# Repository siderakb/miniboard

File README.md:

# Miniboard

A super mini keyboard.

## Disclaimer

These files are provided without warranty of any kind.  
Including but not limited to manufacturing, assembly, procurement and use at your own risk.  
It is recommended to check yourself before use.  

For the full statement, please see [LICENSE](./LICENSE).

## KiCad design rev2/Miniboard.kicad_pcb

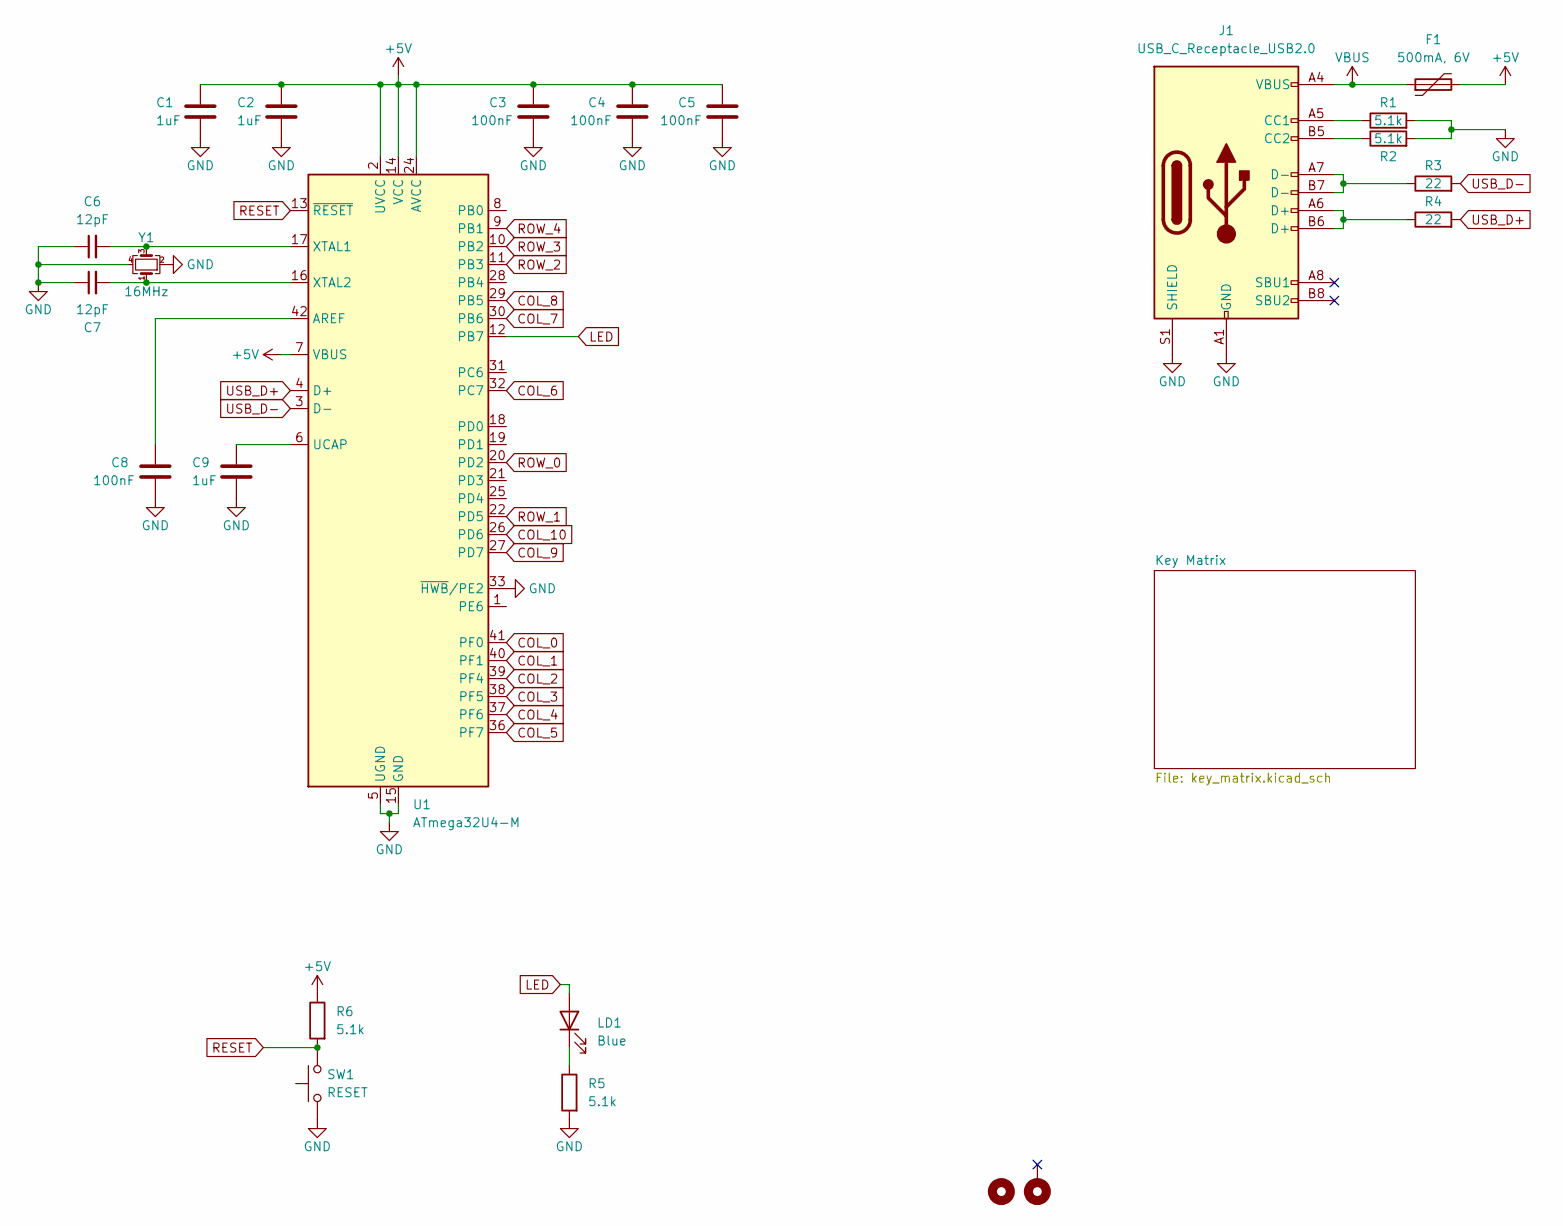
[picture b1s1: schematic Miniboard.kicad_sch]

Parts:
C1, C2, C9: 1uF; C_0402_1005Metric; MFR. Part # CL05A105KA5NQNC; LCSC C52923
C3, C4, C5, C8: 100nF; C_0402_1005Metric; MFR. Part # CL05B104KO5NNNC; LCSC C1525
C6, C7: 12pF; C_0402_1005Metric; MFR. Part # 0402CG120J500NT; LCSC C1547
F1: 500mA, 6V; Fuse_0805_2012Metric; MFR. Part # SMD0805B050TF; LCSC C269104
H2: MountingHole
H3: MountingHole_Pad; MountingHole_2.2mm_M2_DIN965_Pad
J1: USB_C_Receptacle_USB2.0; USB-C_16p_918-418K2023S40023; MFR. Part # 918-418K2023S40023; LCSC C709031
LD1: Blue; LED_0603_1608Metric; MFR. Part # 19-217/GHC-YR1S2/3T; LCSC C72043
R1, R2, R5, R6: 5.1k; R_0402_1005Metric; MFR. Part # 0402WGF5101TCE; LCSC C25905
R3, R4: 22; R_0402_1005Metric; MFR. Part # CRCW040222R0FKED; LCSC C482106
SW1: RESET; SW_SPST_B3U-1000P; MFR. Part # B3U-1000P; LCSC C231329
U1: ATmega32U4-M; QFN-44-1EP_7x7mm_P0.5mm_EP5.2x5.2mm; MFR. Part # ATMEGA32U4-MU; LCSC C112161
Y1: 16MHz; Crystal_SMD_2016-4Pin_2.0x1.6mm; MFR. Part # XL7EL89COI-111YLC-16M; LCSC C2965579

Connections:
+5V: C1.1, C2.1, C3.1, C4.1, C5.1, F1.2, R6.1, U1.2 (UVCC), U1.7 (VBUS), U1.14 (VCC), U1.24 (AVCC), U1.34 (VCC), U1.44 (AVCC)
COL_0: U1.41 (PF0); also elsewhere on the board
COL_1: U1.40 (PF1); also elsewhere on the board
COL_2: U1.39 (PF4); also elsewhere on the board
COL_3: U1.38 (PF5); also elsewhere on the board
COL_4: U1.37 (PF6); also elsewhere on the board
COL_5: U1.36 (PF7); also elsewhere on the board
COL_6: U1.32 (PC7); also elsewhere on the board
COL_7: U1.30 (PB6); also elsewhere on the board
COL_8: U1.29 (PB5); also elsewhere on the board
COL_9: U1.27 (PD7); also elsewhere on the board
COL_10: U1.26 (PD6); also elsewhere on the board
GND: C1.2, C2.2, C3.2, C4.2, C5.2, C6.1, C7.1, C8.2, C9.2, J1.A1 (GND), J1.A12 (GND), J1.B1 (GND), J1.B12 (GND), J1.S1 (SHIELD), R1.2, R2.2, R5.2, SW1.1, U1.5 (UGND), U1.15 (GND), U1.23 (GND), U1.33 (~HWB/PE2), U1.35 (GND), U1.43 (GND), U1.45 (GND), Y1.2, Y1.4
LED: LD1.2 (A), U1.12 (PB7)
unnamed: J1.A5 (CC1), R1.1
unnamed: J1.B5 (CC2), R2.1
unnamed: J1.A6 (D+), J1.B6 (D+), R4.1
unnamed: J1.A7 (D-), J1.B7 (D-), R3.1
unnamed: LD1.1 (K), R5.1
unnamed: C8.1, U1.42 (AREF)
unnamed: C9.1, U1.6 (UCAP)
unnamed: C6.2, U1.17 (XTAL1), Y1.3
unnamed: C7.2, U1.16 (XTAL2), Y1.1
RESET: R6.2, SW1.2, U1.13 (~RESET)
ROW_0: U1.20 (PD2); also elsewhere on the board
ROW_1: U1.22 (PD5); also elsewhere on the board
ROW_2: U1.11 (PB3); also elsewhere on the board
ROW_3: U1.10 (PB2); also elsewhere on the board
ROW_4: U1.9 (PB1); also elsewhere on the board
USB_D+: R4.2, U1.4 (D+)
USB_D-: R3.2, U1.3 (D-)
VBUS: F1.1, J1.A4 (VBUS), J1.A9 (VBUS), J1.B4 (VBUS), J1.B9 (VBUS)

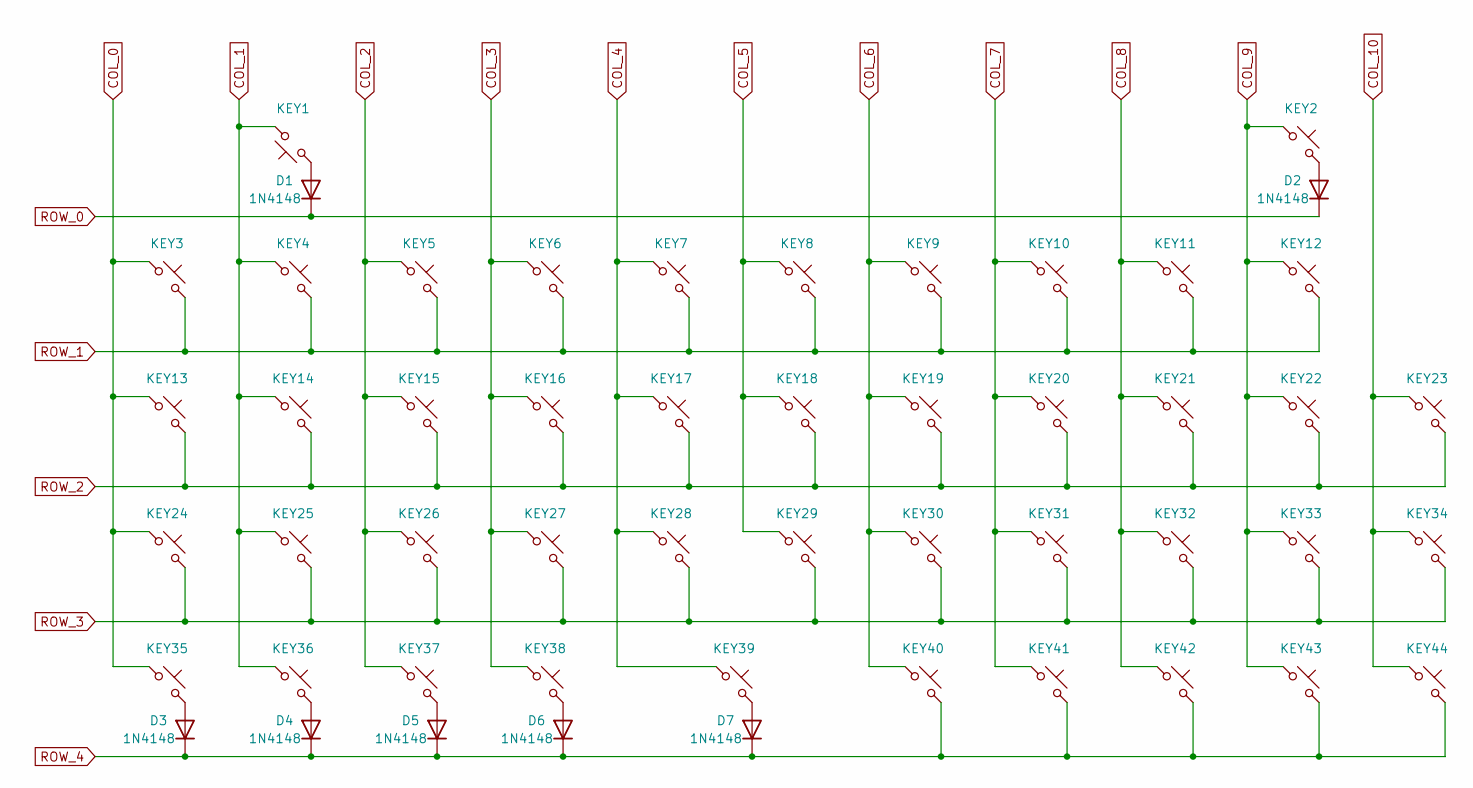
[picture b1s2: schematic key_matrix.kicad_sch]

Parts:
D1, D2, D3, D4, D5, D6, D7: 1N4148; D_SOD-323_HandSoldering; MFR. Part # 1N4148WS; LCSC C2128
KEY1, KEY2: SW_Push_45deg; SW_2x4x3.5mm_side; MFR. Part # TS24CA; LCSC C393942
KEY3, KEY4, KEY5, KEY6, KEY7, KEY8, KEY9, KEY10, KEY11, KEY12, KEY13, KEY14, KEY15, KEY16, KEY17, KEY18, KEY19, KEY20, KEY21, KEY22, KEY23, KEY24, KEY25, KEY26, KEY27, KEY28, KEY29, KEY30, KEY31, KEY32, KEY33, KEY34, KEY35, KEY36, KEY37, KEY38, KEY39, KEY40, KEY41, KEY42, KEY43, KEY44: SW_Push_45deg; SW_1TS015A; MFR. Part # 1TS015A-1800-0600-CT; LCSC C256105

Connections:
COL_0: KEY3.1, KEY13.1, KEY24.1, KEY35.1; also elsewhere on the board
COL_1: KEY1.2, KEY4.1, KEY14.1, KEY25.1, KEY36.1; also elsewhere on the board
COL_2: KEY5.1, KEY15.1, KEY26.1, KEY37.1; also elsewhere on the board
COL_3: KEY6.1, KEY16.1, KEY27.1, KEY38.1; also elsewhere on the board
COL_4: KEY7.1, KEY17.1, KEY28.1, KEY39.1; also elsewhere on the board
COL_5: KEY8.1, KEY18.1, KEY29.1; also elsewhere on the board
COL_6: KEY9.1, KEY19.1, KEY30.1, KEY40.1; also elsewhere on the board
COL_7: KEY10.1, KEY20.1, KEY31.1, KEY41.1; also elsewhere on the board
COL_8: KEY11.1, KEY21.1, KEY32.1, KEY42.1; also elsewhere on the board
COL_9: KEY2.1, KEY12.1, KEY22.1, KEY33.1, KEY43.1; also elsewhere on the board
COL_10: KEY23.1, KEY34.1, KEY44.1; also elsewhere on the board
unnamed: D1.2 (A), KEY1.1
unnamed: D2.2 (A), KEY2.2
unnamed: D3.2 (A), KEY35.2
unnamed: D4.2 (A), KEY36.2
unnamed: D5.2 (A), KEY37.2
unnamed: D6.2 (A), KEY38.2
unnamed: D7.2 (A), KEY39.2
ROW_0: D1.1 (K), D2.1 (K); also elsewhere on the board
ROW_1: KEY3.2, KEY4.2, KEY5.2, KEY6.2, KEY7.2, KEY8.2, KEY9.2, KEY10.2, KEY11.2, KEY12.2; also elsewhere on the board
ROW_2: KEY13.2, KEY14.2, KEY15.2, KEY16.2, KEY17.2, KEY18.2, KEY19.2, KEY20.2, KEY21.2, KEY22.2, KEY23.2; also elsewhere on the board
ROW_3: KEY24.2, KEY25.2, KEY26.2, KEY27.2, KEY28.2, KEY29.2, KEY30.2, KEY31.2, KEY32.2, KEY33.2, KEY34.2; also elsewhere on the board
ROW_4: D3.1 (K), D4.1 (K), D5.1 (K), D6.1 (K), D7.1 (K), KEY40.2, KEY41.2, KEY42.2, KEY43.2, KEY44.2; also elsewhere on the board

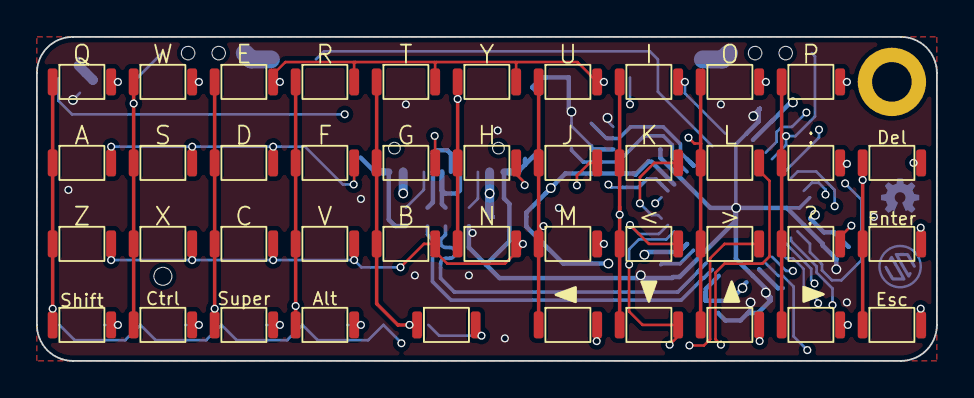
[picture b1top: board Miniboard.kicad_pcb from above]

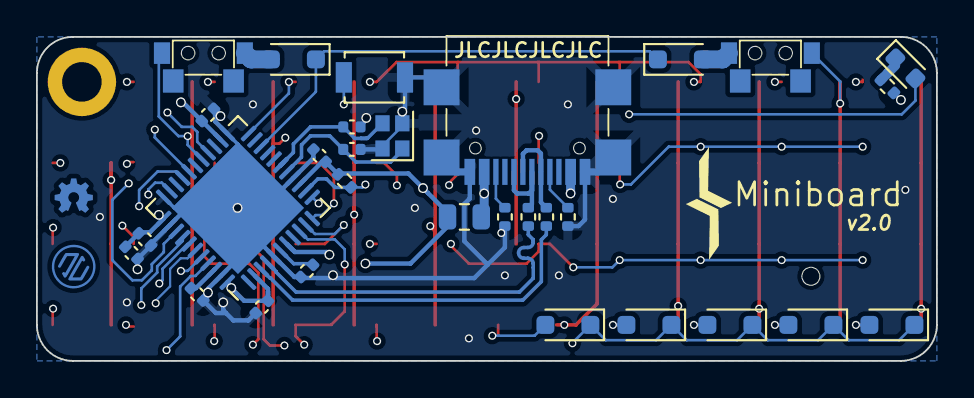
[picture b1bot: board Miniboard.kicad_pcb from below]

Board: 4 copper layers, 50.0 x 18.0 mm, 74 parts (30 on the bottom side), 39 nets.

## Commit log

2023-06-22 Init commit
2023-06-23 Routed
2023-06-23 Move rev1 PCB files
2023-06-23 Rev2.0 init
2023-06-25 Add keyboard-layout-editor json
2023-06-25 Update Rev2
2023-06-25 Update Rev1.0 silkscreen
2023-06-25 Add README.md
2023-06-25 Create LICENSE
2023-07-08 Update BOM

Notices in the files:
Miniboard.kicad_sch:
MIT License (Open source hardware)
